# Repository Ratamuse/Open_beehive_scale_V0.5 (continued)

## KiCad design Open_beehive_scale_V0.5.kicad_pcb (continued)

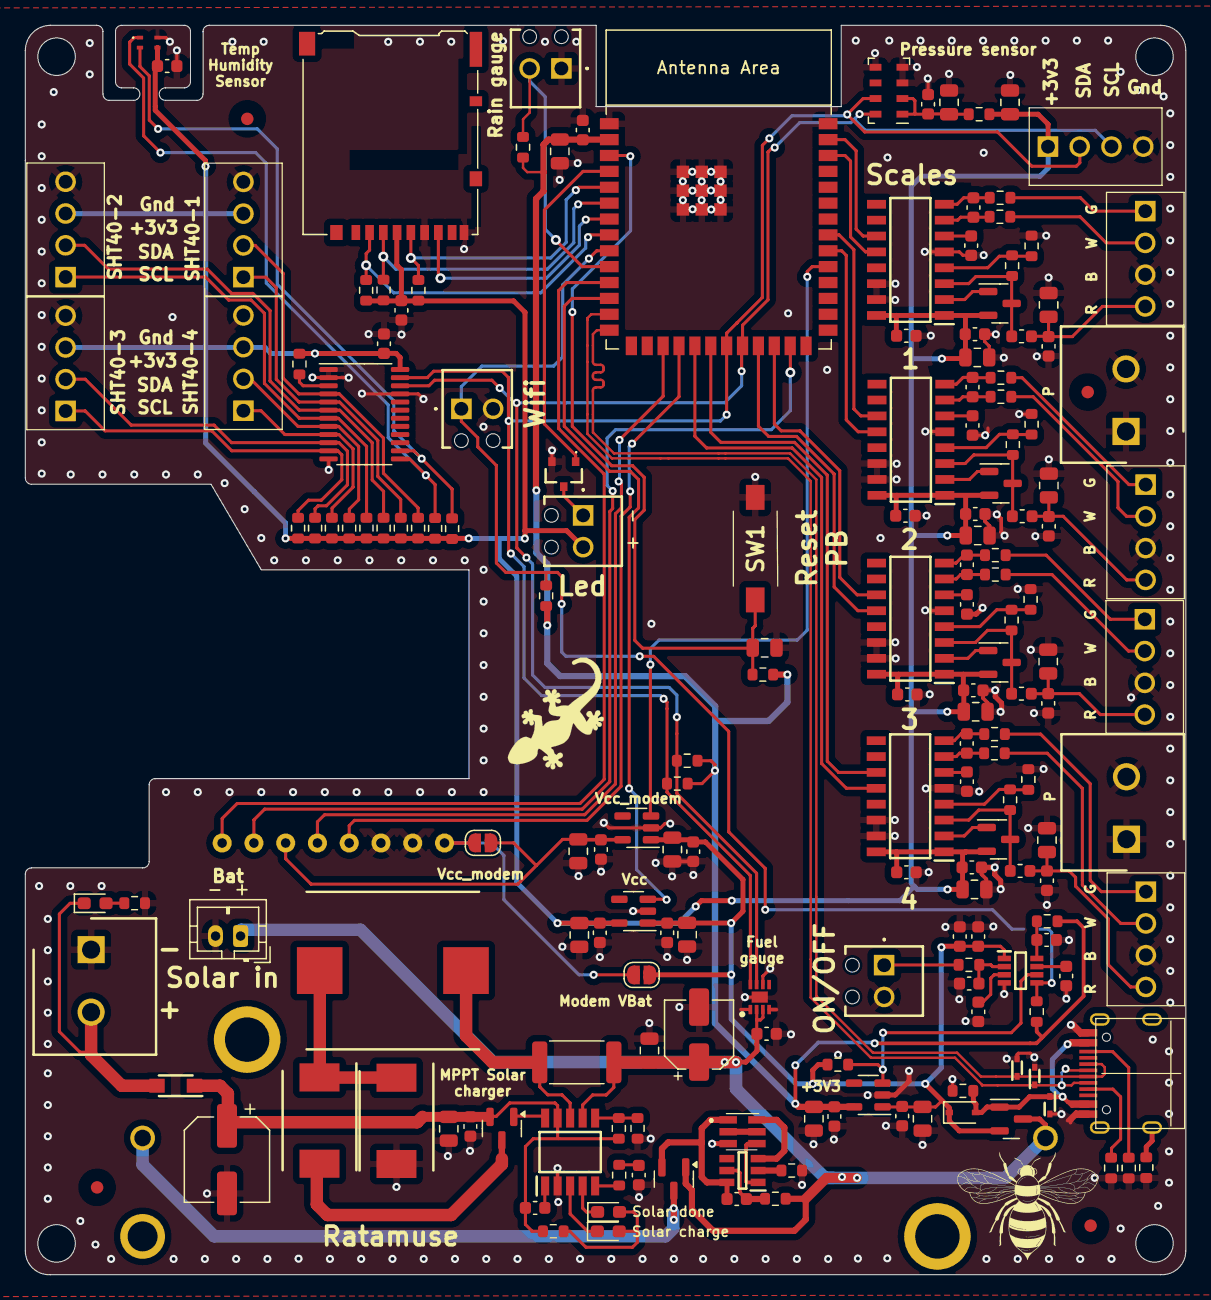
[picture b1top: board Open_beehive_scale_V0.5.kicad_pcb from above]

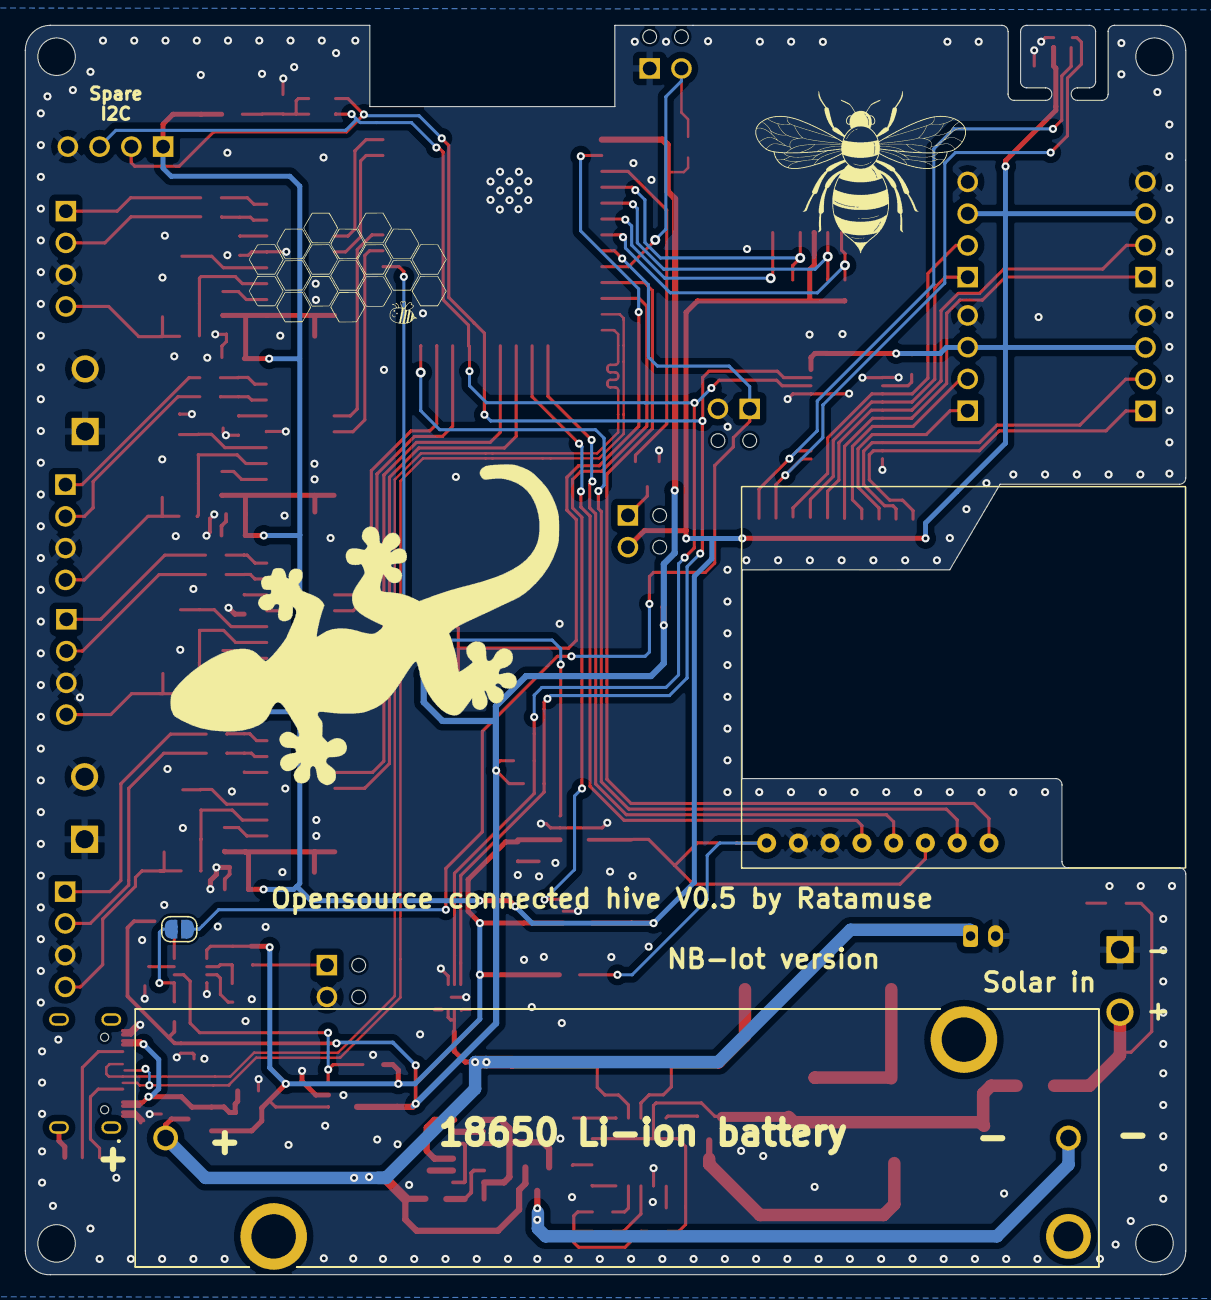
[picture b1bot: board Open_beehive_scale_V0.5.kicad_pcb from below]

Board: 2 copper layers, 92.8 x 99.9 mm, 184 parts (2 on the bottom side), 114 nets.

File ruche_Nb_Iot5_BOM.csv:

Reference,Value,Footprint,Qty,DNP
C1,100µF/35V,Capacitor_SMD:CP_Elec_6.3x7.7,1,
C2,470nF/50V,Capacitor_SMD:C_0603_1608Metric,1,
C3,4.7µF/50V,Capacitor_SMD:C_0805_2012Metric,1,
C4,220nF,Capacitor_SMD:C_0603_1608Metric,1,
"C5,C10,C11,C14,C15,C17,C19,C20,C22,C23,C26,C27,C28,C29,C30,C31,C32,C33,C36,C37,C40,C41,C42,C43,C44,C45,C46,C47,C50,C52,C53,C58,C61,C62,C64",0.1µF,-- valeurs mixtées --,35,
C6,1µF,Capacitor_SMD:C_0603_1608Metric,1,
C7,0.1µF/50V,Capacitor_SMD:C_0603_1608Metric,1,
"C8,C9,C12,C13,C16,C18,C24,C25,C34,C35,C38,C39,C48,C49,C51,C54,C60,C63",10µF,-- valeurs mixtées --,18,
"C21,C55",0.150µF,Capacitor_SMD:C_0603_1608Metric,2,
C56,0.010µF,Capacitor_SMD:C_0603_1608Metric,1,
"C57,C59",22µF,Capacitor_SMD:C_0805_2012Metric,2,
"D1,D3,D4",LED,LED_SMD:LED_0603_1608Metric_Pad1.05x0.95mm_HandSolder,3,
D2,MBR230LSFT1G,Empreintes:SODFL3616X98N,1,
"D5,D6",SS34,Empreintes:DIOM8059X256N,2,
"D10,D11,D12",SP1003-01DTG,Empreintes:SODFL1406X65N,3,
D14,D_Schottky,Diode_SMD:D_SOD-323,1,
FB1,FerriteBead,Resistor_SMD:R_0603_1608Metric,1,
IC1,CN3791,Empreintes:SOP100P600X175-10N,1,
IC2,MAX17048G+,Empreintes:SON50P200X200X80-9N-D,1,
IC3,LTC2954CTS8-1#TRMPBF,Empreintes:SOT65P280X100-8N,1,
IC4,SHT41-AD1B-R3,Empreintes:SHT41AD1BR3,1,
"IC5,IC6,IC7,IC8",HX711,Empreintes:SOIC127P600X160-16N,4,
IC9,FS312F-G,Empreintes:SOT95P280X145-6N,1,
"J1,J3,J4,J6,J7,J8,J9,J21",Conn_01x02,-- valeurs mixtées --,8,
"J2,J5,J10,J11,J12,J15,J16,J17,J18",Conn_01x04,Empreintes:1725672,9,
J13,Micro_SD_Card,Connector_Card:microSD_HC_Hirose_DM3AT-SF-PEJM5,1,
J20,USB_C_Receptacle_USB2.0 USB4105-GF-A ,Empreintes:TYPE-C-31-M-12,1,
J22,Conn_01x08,Empreintes:Sim8070G,1,
"JP2,JP3,JP4",Jumper_2_Open,Jumper:SolderJumper-2_P1.3mm_Open_RoundedPad1.0x1.5mm,3,
L1,82µH/3A,Empreintes:INDPM138126X700N,1,
"L2,L3,L4,L5",3.3µH,Inductor_SMD:L_0603_1608Metric,4,
Q1,AO3401A,Package_TO_SOT_SMD:SOT-23,1,
"Q2,Q3,Q4,Q5",MMBT4403,Package_TO_SOT_SMD:SOT-23,4,
Q6,"PMBT2222A,215",Empreintes:PMBT2222A215,1,
Q7,DMG2301L,Package_TO_SOT_SMD:SOT-23,1,
Q8,FS8205,Empreintes:FS8205,1,
Q10,AO3400,Package_TO_SOT_SMD:SOT-23,1,
"R1,R3,R4,R32,R33,R34,R35,R36,R37,R38,R39,R40,R42,R48,R49,R50,R51",10K,Resistor_SMD:R_0603_1608Metric,17,
R2,120,Resistor_SMD:R_0603_1608Metric,1,
R5,30K,Resistor_SMD:R_0603_1608Metric,1,
R6,0.24R,Resistor_SMD:R_2512_6332Metric,1,
"R7,R8",2.2K,Resistor_SMD:R_0603_1608Metric,2,
R9,100K,Resistor_SMD:R_0603_1608Metric,1,
"R10,R43",100k,Resistor_SMD:R_0603_1608Metric,2,
"R12,R19,R23,R27",20K,Resistor_SMD:R_0603_1608Metric,4,
"R13,R14,R15",10k,Resistor_SMD:R_0603_1608Metric,3,
"R16,R20,R24,R28",8.2K,Resistor_SMD:R_0603_1608Metric,4,
"R17,R18,R21,R22,R25,R26,R29,R30,R53",100,Resistor_SMD:R_0603_1608Metric,9,
R31,1M,Resistor_SMD:R_0603_1608Metric,1,
"R41,R45,R46",5.1K,Resistor_SMD:R_0603_1608Metric,3,
R52,1K,Resistor_SMD:R_0603_1608Metric,1,
SW1,SW_Push,Empreintes:PTS636SL43SMTRLFS,1,
U2,MS5611-01BA,Package_LGA:LGA-8_3x5mm_P1.25mm,1,
"U3,U5,U9",XC6220B331MR,Package_TO_SOT_SMD:SOT-23-5,3,
U4,TCA9548APWR,Package_SO:TSSOP-24_4.4x7.8mm_P0.65mm,1,
U7,1043,Empreintes:1043,1,
U8,ESP32-S3-WROOM-1,Espressif:ESP32-S3-WROOM-1,1,
